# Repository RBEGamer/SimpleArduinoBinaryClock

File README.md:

# SimpleArduinoBinaryClock
Arduino based binary clock with hours and minutes display, nightmode and alarm.
It uses a Arsuino Nano and the WS2812 Leds,to show the time in a binary format.
The time, alarm time and nightmode time, can be set by the 4 switches on the back of the clock.
With the top button, you can change the color and stop the ringing alarm.
In my version of the clock, it comes with a 10x10x10cm  acryl plasic case.

# PARTS ELECTRONICS
* WS2813 led strip with 16 leds
* Any Arduino based board, but use a small one for a small case
* I2C RTC module (i use the DS3231 or you can use the DS1307)
* 5V Power supply or you power it with usb
* 5 Pushbuttons
* mini speaker
* 5 320 Ohm Pull-UP-Resistors

# TOOLS
* Solder equipment
* Knife
* Arcyl Glue
* Hotglue
* Wires
* Drill 6mm (depend on your button size)
* Dill 3mm (for the power cable-9

# PARTS CASE (10x10x10cm)
* 1 90x100x3mm LED PLATE
* 2 106x106x3mm at 75% transparency, FRONT PLATE
* 2 100x100x3mm LEDT/RIGHT PLATE
* 2 106x106x3mm TOP/BOTTOM PLATE

# SOFTWARE SETUP
* Download the sketch, lpcated on /CODE/beta_7_final.zip
* Download the latest Arduino IDE
* Download the Adafruit-Neopixel libary

# BUILD YOUR CLOCK
* Cut the ES2812 into 4 strips with 4 leds each
* Glue the 4 strips parallel to each other in the center of the LED PLATE
* Connect to the DI,VCC,GND pins of the right led strip 3x 5cm Wires (for the connection to the arduino)
* Now connect from right to left, DOUT to DI og the next left led strip
* at least connect to all strips, VCC and Gound
* Connect the VCC and Ground of the RTC Module to Arduino
* Connect the I2C pins to the Arduino. SCL(RTC) to A5 (SCL,ARDUINO) and SDA(RTC) to A4(SDA,Arduino)
* Connect VCC, Ground from the led strips to the Arduino
* Connect the DI of the led strips to D7 of the Arduino
* Connect on pin of the mini speaker to ground and the other to pin D13 of the Aduino
* Solder on each Button 3 Wires, on one pin two wires and on the other only one wire
* Connect the single wire of each button to Ground
* Solder of one of the two wires the pullup resistor and connect these to VCC(5V)
* Connect the last wire of each button to : D6 (sone alarm), D5(set alarm), D4 (set time), D2(add), D3(sub)

Now we are finih with the soldering, now we are building the case

* Drill to the BACK PLATE 4 holes for the switches: SET_ALARM, SET_TIME, ADD, SUB
* Drill a hole to the center of the TOP PLATE for the SONE switch
* Drill a second hole into the TOP PLATE for the speaker
* Drill a small hole into one of the bottom corners of the BACK PLATE for the power cable
* Place the switches at the right holes
* Glue the speaker next to the second hole of the TOP PLATE
* Glue the LED PLATE to the FRONT PLATE
* Glue the Arduino and the RTC Module to the back of the LED PLATE
* Assemble the other Plate around the bottom plate to get a cube

Now your clock is ready to use!!
Have FUN!

# SCHEMATIC AND PCB
I am currently working on a pcb for the clock. The KICAT file can be found at `src/bin_clock_kicad/`.

# IMAGES

Deatiled images of the build process, can be found at the /IMAGES folder

### FINAL CLOCK

### Final hardware with connected buttons

### placed WS2812 LED Strips

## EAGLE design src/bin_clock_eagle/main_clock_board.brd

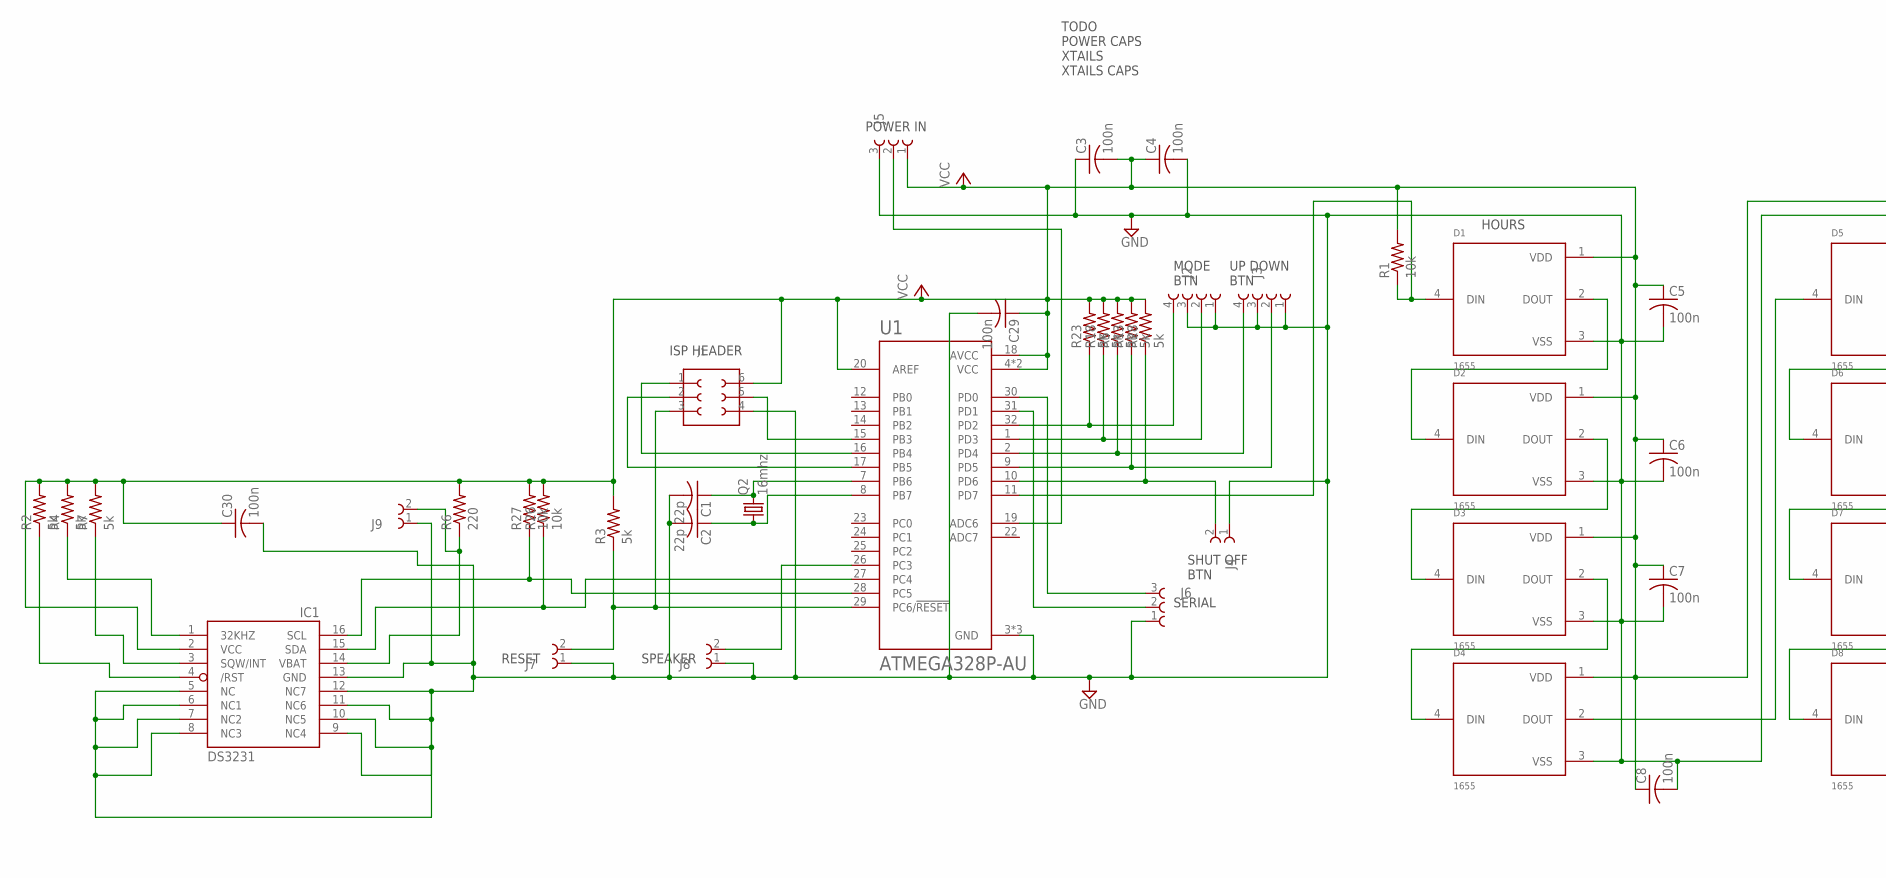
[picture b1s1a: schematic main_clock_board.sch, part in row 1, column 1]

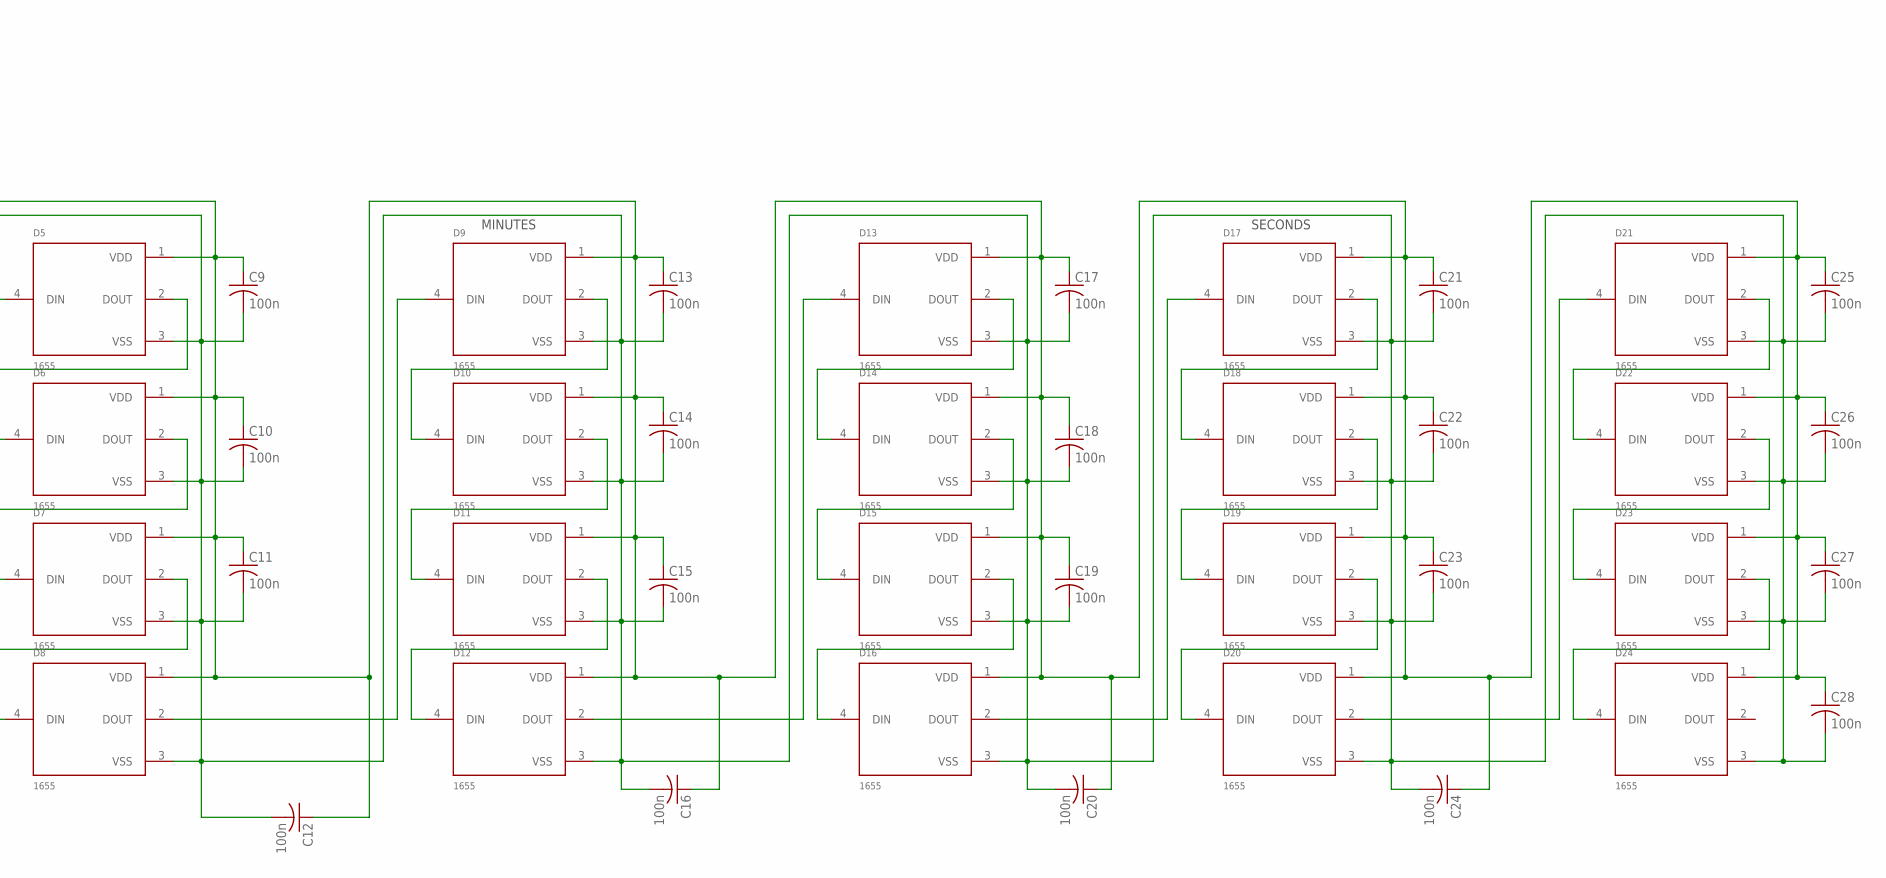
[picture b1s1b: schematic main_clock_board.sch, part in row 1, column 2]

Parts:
C1, C2: 22p; C0603
C3, C4, C5, C6, C7, C8, C9, C10, C11, C12, C13, C14, C15, C16, C17, C18, C19, C20, C21, C22, C23, C24, C25, C26, C27, C28, C29, C30: 100n; C025-024X044
D1, D2, D3, D4, D5, D6, D7, D8, D9, D10, D11, D12, D13, D14, D15, D16, D17, D18, D19, D20, D21, D22, D23, D24: 1655; FCI_1655
IC1: DS3231/SO; SO16W
J1: 610X0621121
J2, J3: 61300411121
J4, J7, J8, J9: 61300211121
J5, J6: 61300311121
Q2: 16mhz; HC49/S
R1, R26, R27: 10k; R0603
R2, R3, R4, R5, R7, R13, R18, R23, R28: 5k; R0603
R6: 220; R0603
U1: ATMEGA328P-AU; QFP80P900X900X120-32N

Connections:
GND: C1.2, C2.2, C3.1, C4.2, C5.2, C6.2, C7.2, C8.2, C9.2, C10.2, C11.2, C12.2, C13.2, C14.2, C15.2, C16.2, C17.2, C18.2, C19.2, C20.2, C21.2, C22.2, C23.2, C24.2, C25.2, C26.2, C27.2, C28.2, C29.2, C30.2, D1.3 (VSS), D2.3 (VSS), D3.3 (VSS), D4.3 (VSS), D5.3 (VSS), D6.3 (VSS), D7.3 (VSS), D8.3 (VSS), D9.3 (VSS), D10.3 (VSS), D11.3 (VSS), D12.3 (VSS), D13.3 (VSS), D14.3 (VSS), D15.3 (VSS), D16.3 (VSS), D17.3 (VSS), D18.3 (VSS), D19.3 (VSS), D20.3 (VSS), D21.3 (VSS), D22.3 (VSS), D23.3 (VSS), D24.3 (VSS), IC1.5 (NC), IC1.6 (NC1), IC1.7 (NC2), IC1.8 (NC3), IC1.9 (NC4), IC1.10 (NC5), IC1.11 (NC6), IC1.12 (NC7), IC1.13 (GND), J1.4, J2.1 (4), J2.3 (2), J3.1 (4), J3.3 (2), J4.1, J5.3 (1), J6.1 (3), J7.1, J8.1, J9.1, U1.3 (GND), U1.5 (GND), U1.21 (GND)
unnamed: D1.2 (DOUT), D2.4 (DIN)
unnamed: IC1.15 (SDA), R26.1, U1.27 (PC4)
unnamed: D2.2 (DOUT), D3.4 (DIN)
unnamed: D3.2 (DOUT), D4.4 (DIN)
unnamed: D4.2 (DOUT), D5.4 (DIN)
unnamed: D5.2 (DOUT), D6.4 (DIN)
unnamed: D6.2 (DOUT), D7.4 (DIN)
unnamed: D7.2 (DOUT), D8.4 (DIN)
unnamed: IC1.16 (SCL), R27.1, U1.28 (PC5)
unnamed: J1.3, J7.2, R3.1, U1.29 (PC6/!RESET)
unnamed: D8.2 (DOUT), D9.4 (DIN)
unnamed: D9.2 (DOUT), D10.4 (DIN)
unnamed: J1.1, U1.16 (PB4)
unnamed: IC1.4 (/RST), R2.1
unnamed: D10.2 (DOUT), D11.4 (DIN)
unnamed: D11.2 (DOUT), D12.4 (DIN)
unnamed: D12.2 (DOUT), D13.4 (DIN)
unnamed: D13.2 (DOUT), D14.4 (DIN)
unnamed: D14.2 (DOUT), D15.4 (DIN)
unnamed: D15.2 (DOUT), D16.4 (DIN)
unnamed: J2.4 (1), R23.1, U1.32 (PD2)
unnamed: D16.2 (DOUT), D17.4 (DIN)
unnamed: D17.2 (DOUT), D18.4 (DIN)
unnamed: J1.2, U1.17 (PB5)
unnamed: J2.2 (3), R18.1, U1.1 (PD3)
unnamed: D18.2 (DOUT), D19.4 (DIN)
unnamed: D19.2 (DOUT), D20.4 (DIN)
unnamed: D20.2 (DOUT), D21.4 (DIN)
unnamed: D21.2 (DOUT), D22.4 (DIN)
unnamed: D22.2 (DOUT), D23.4 (DIN)
unnamed: D23.2 (DOUT), D24.4 (DIN)
unnamed: J3.4 (1), R5.1, U1.2 (PD4)
unnamed: J3.2 (3), R13.1, U1.9 (PD5)
unnamed: D1.4 (DIN), R1.1, U1.11 (PD7)
unnamed: J4.2, R28.1, U1.10 (PD6)
unnamed: J1.5, U1.15 (PB3)
unnamed: J6.2, U1.31 (PD1)
unnamed: J6.3 (1), U1.30 (PD0)
unnamed: J5.2, U1.19 (ADC6)
unnamed: J8.2, U1.26 (PC3)
unnamed: IC1.1 (32KHZ), R4.1
unnamed: IC1.14 (VBAT), J9.2, R6.1
unnamed: IC1.3 (SQW/INT), R7.1
unnamed: C1.1, Q2.2, U1.7 (PB6)
unnamed: C2.1, Q2.1, U1.8 (PB7)
VCC: C3.2, C4.1, C5.1, C6.1, C7.1, C8.1, C9.1, C10.1, C11.1, C12.1, C13.1, C14.1, C15.1, C16.1, C17.1, C18.1, C19.1, C20.1, C21.1, C22.1, C23.1, C24.1, C25.1, C26.1, C27.1, C28.1, C29.1, C30.1, D1.1 (VDD), D2.1 (VDD), D3.1 (VDD), D4.1 (VDD), D5.1 (VDD), D6.1 (VDD), D7.1 (VDD), D8.1 (VDD), D9.1 (VDD), D10.1 (VDD), D11.1 (VDD), D12.1 (VDD), D13.1 (VDD), D14.1 (VDD), D15.1 (VDD), D16.1 (VDD), D17.1 (VDD), D18.1 (VDD), D19.1 (VDD), D20.1 (VDD), D21.1 (VDD), D22.1 (VDD), D23.1 (VDD), D24.1 (VDD), IC1.2 (VCC), J1.6, J5.1 (3), R1.2, R2.2, R3.2, R4.2, R5.2, R6.2, R7.2, R13.2, R18.2, R23.2, R26.2, R27.2, R28.2, U1.4 (VCC), U1.6 (VCC), U1.18 (AVCC), U1.20 (AREF)

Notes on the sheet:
ISP HEADER
MODE BTN
UP DOWN BTN
SHUT OFF BTN
HOURS
MINUTES
SECONDS
SERIAL
RESET
SPEAKER
TODO POWER CAPS XTAILS XTAILS CAPS
POWER IN

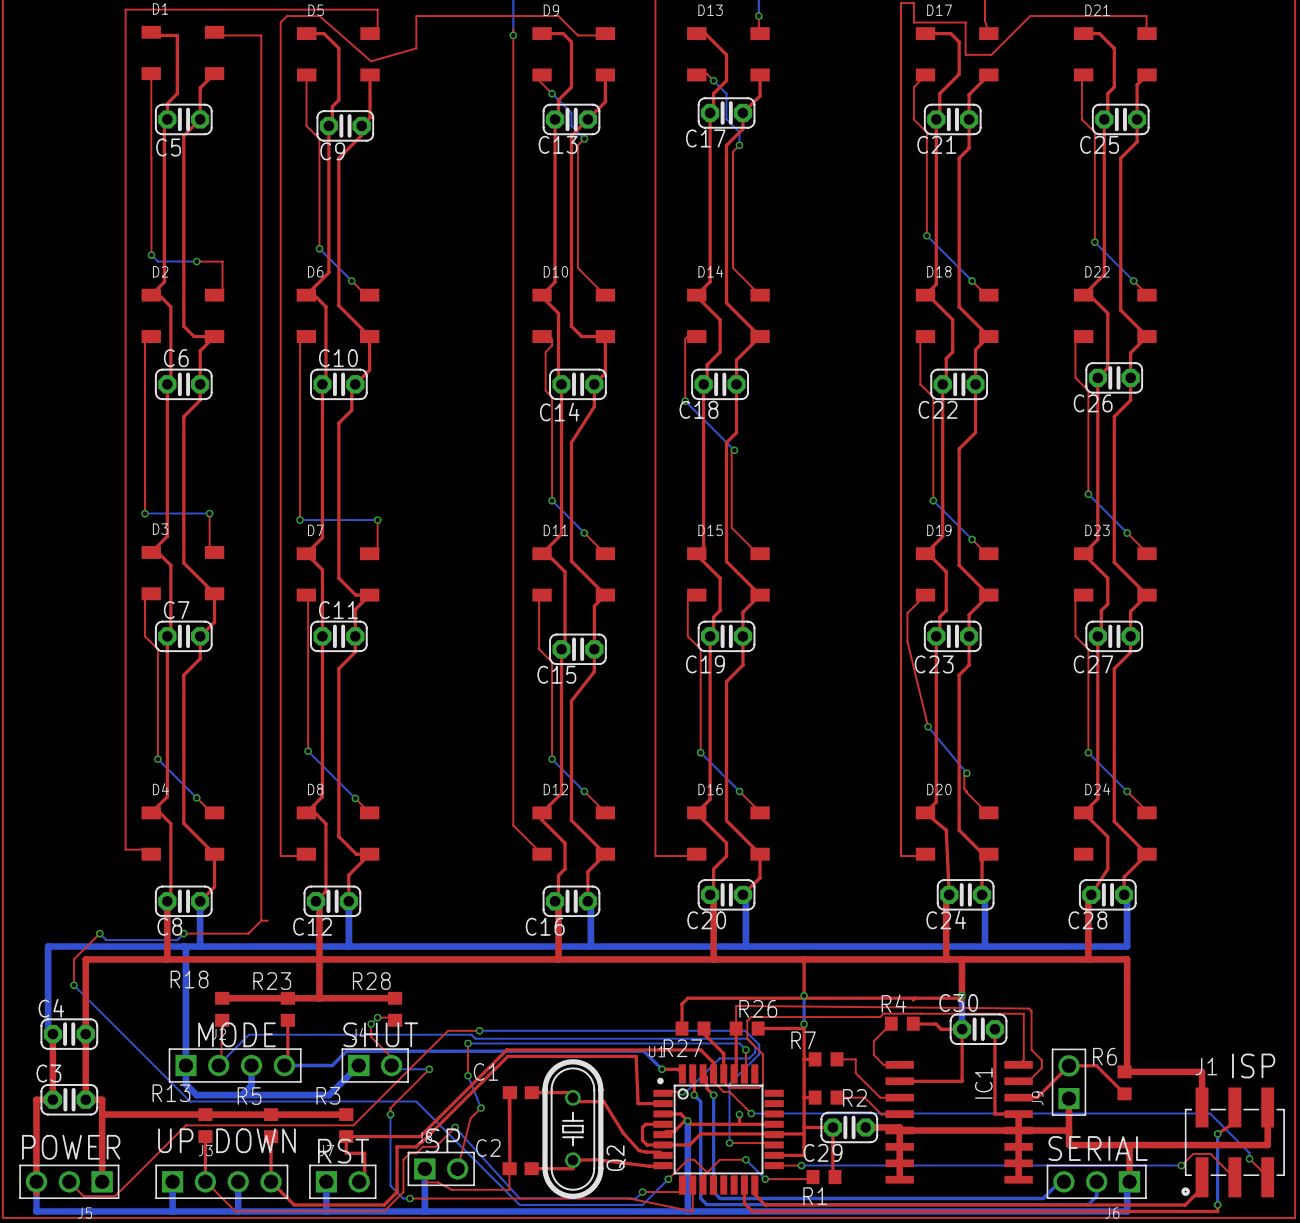
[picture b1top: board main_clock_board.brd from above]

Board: 2 copper layers, 79 parts (0 on the bottom side), 47 nets.

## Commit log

2015-07-25 initial
2017-06-02 added kicad files
2017-06-03 added missing sone button
2017-06-03 added all leds
2017-06-03 added fist pcb board
2017-06-03 pcb rework needed
2017-06-03 added final schematic in eagle
    please use the egale project first.
    feel free to complete the kicad
2017-06-04 added vcc gnd pins
2017-06-05 added part values
2017-06-05 pcb size rework
2017-06-05 added v0 gerber files
2017-06-07 added gound planes
2017-06-07 DRC check ok
2017-06-07 skilscreen correction
2017-06-08 fixed ds3231 package to SO16W
2017-06-08 fixing r4,r7
2017-06-09 added fin gerb files

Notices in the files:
parts and their libraries:
Wurth_Elektronik_Electromechanic_Board_t: Copyright: Würth Elektronik
